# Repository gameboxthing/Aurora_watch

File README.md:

# Aurora_watch
repo for aurora forecast gadget

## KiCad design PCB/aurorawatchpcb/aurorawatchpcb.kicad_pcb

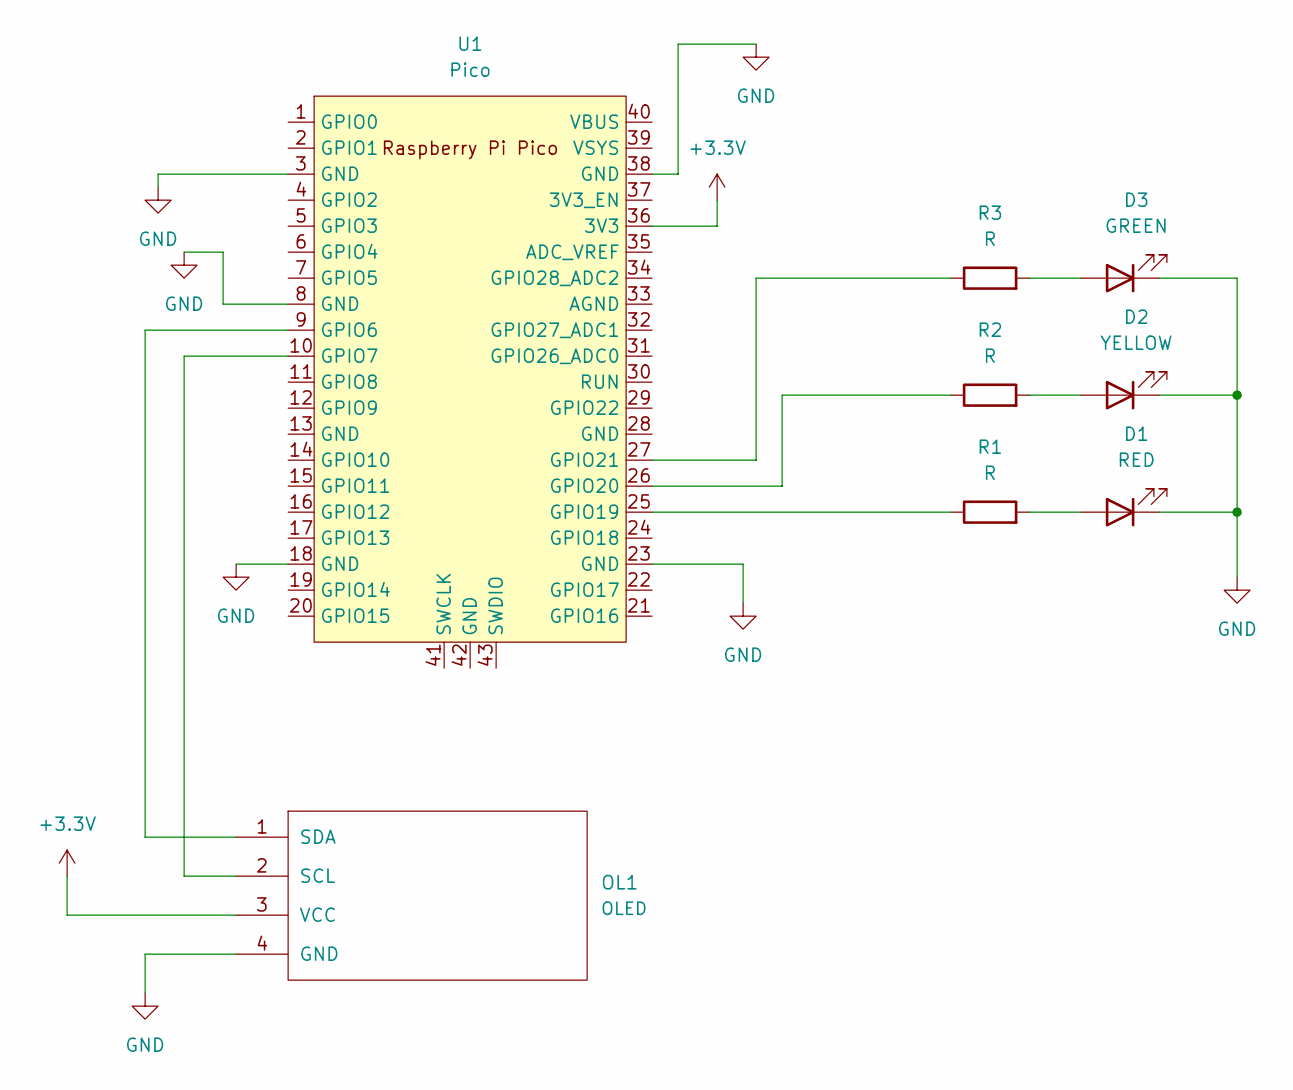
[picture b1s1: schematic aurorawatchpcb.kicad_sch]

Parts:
D1: RED; LED_1206_3216Metric_Pad1.42x1.75mm_HandSolder
D2: YELLOW; LED_1206_3216Metric_Pad1.42x1.75mm_HandSolder
D3: GREEN; LED_1206_3216Metric_Pad1.42x1.75mm_HandSolder
OL1: OLED
R1, R2, R3: R; R_1206_3216Metric_Pad1.30x1.75mm_HandSolder
U1: Pico; RPi_Pico_SMD_TH

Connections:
+3.3V: OL1.3 (VCC), U1.36 (3V3)
GND: D1.1 (K), D2.1 (K), D3.1 (K), OL1.4 (GND), U1.3 (GND), U1.8 (GND), U1.18 (GND), U1.23 (GND), U1.38 (GND)
unnamed: D1.2 (A), R1.2
unnamed: D2.2 (A), R2.2
unnamed: D3.2 (A), R3.2
unnamed: OL1.2 (SCL), U1.10 (GPIO7)
unnamed: OL1.1 (SDA), U1.9 (GPIO6)
unnamed: R1.1, U1.25 (GPIO19)
unnamed: R2.1, U1.26 (GPIO20)
unnamed: R3.1, U1.27 (GPIO21)

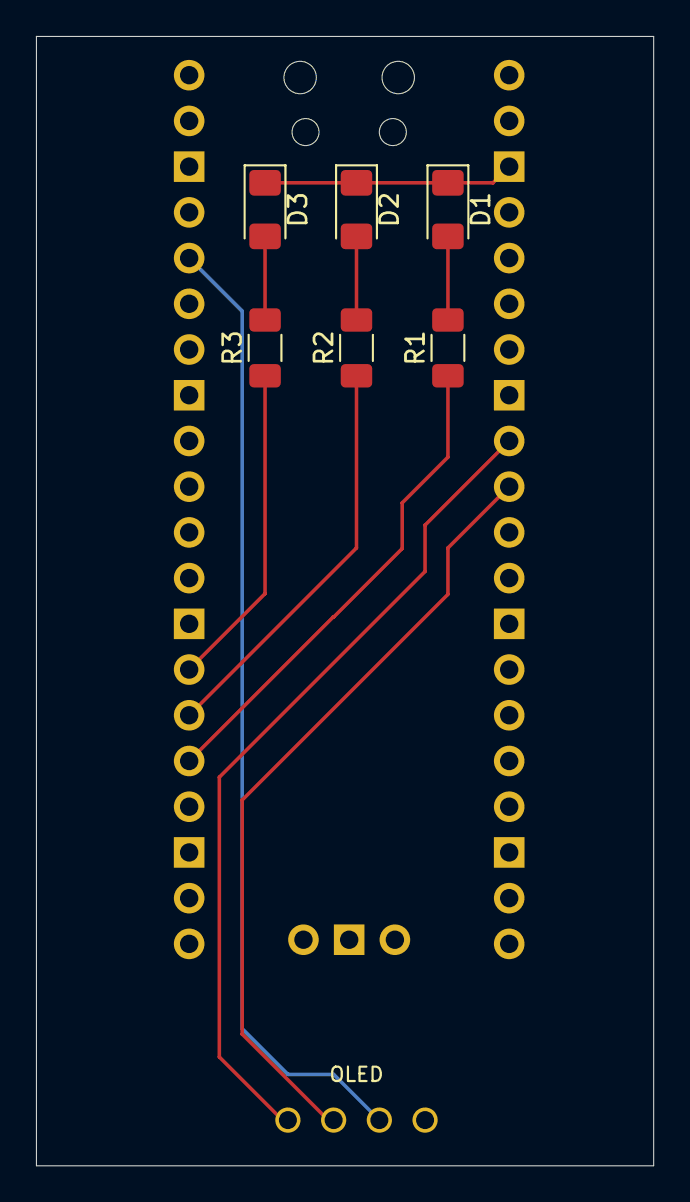
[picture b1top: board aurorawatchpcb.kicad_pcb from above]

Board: 2 copper layers, 34.3 x 62.7 mm, 8 parts (1 on the bottom side), 10 nets.

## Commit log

2025-11-14 PCB: added pcb desgins
